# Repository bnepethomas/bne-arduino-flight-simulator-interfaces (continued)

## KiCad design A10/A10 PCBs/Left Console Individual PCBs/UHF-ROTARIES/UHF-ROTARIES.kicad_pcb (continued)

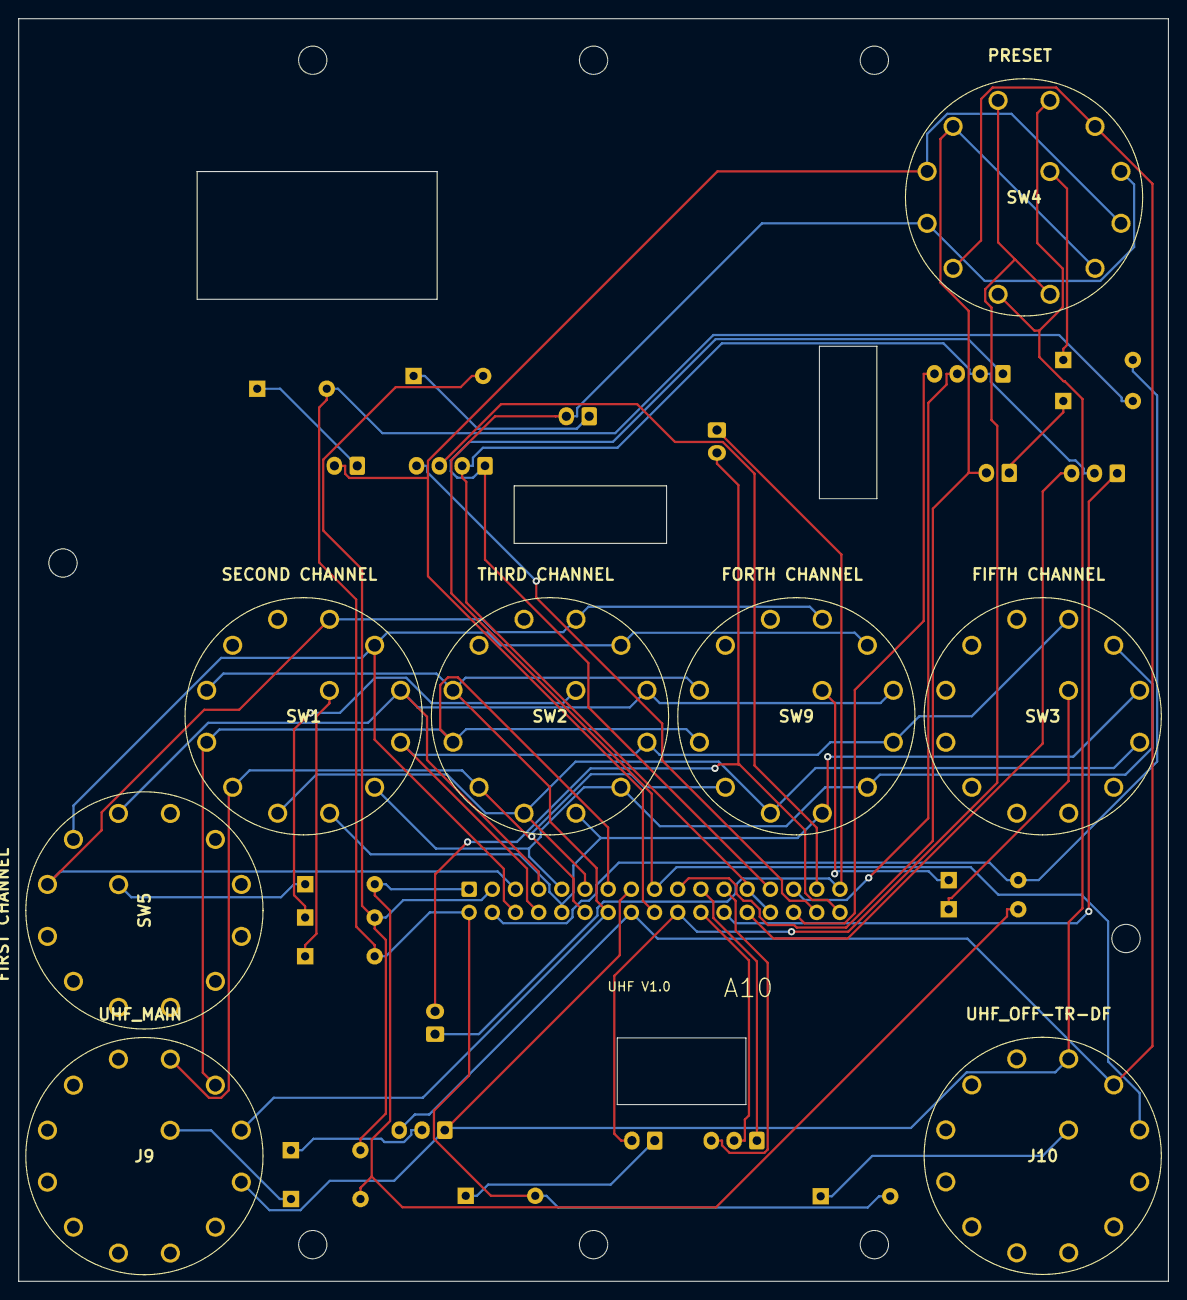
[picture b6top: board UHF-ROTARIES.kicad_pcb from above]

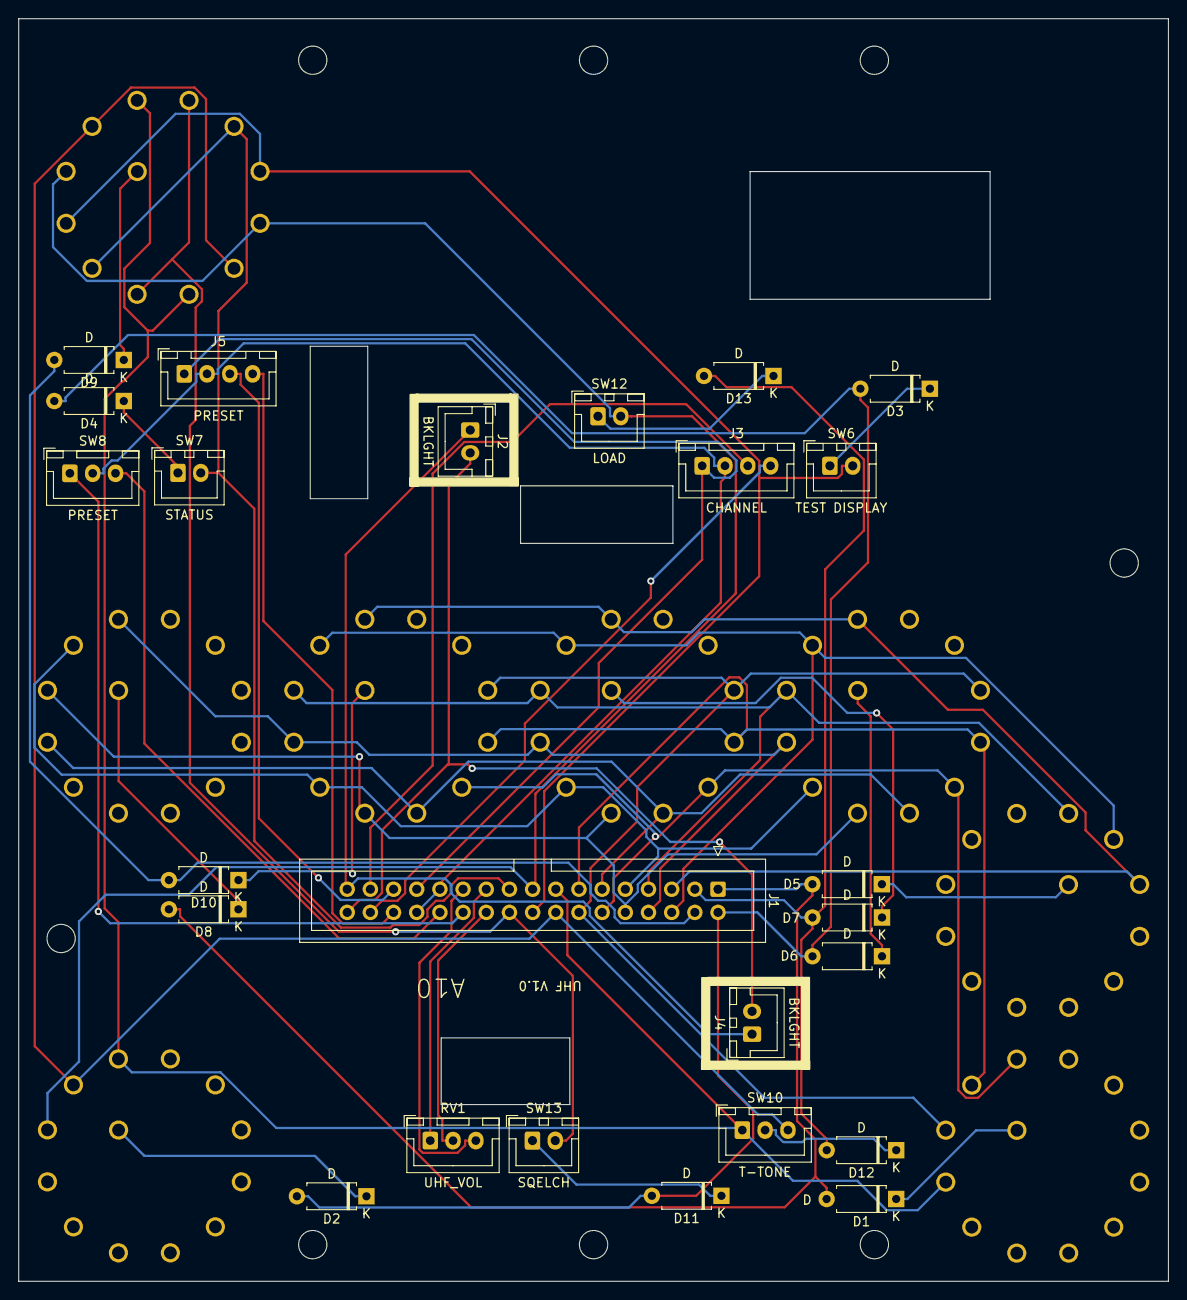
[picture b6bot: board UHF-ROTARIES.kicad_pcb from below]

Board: 2 copper layers, 126.0 x 138.4 mm, 33 parts (25 on the bottom side), 46 nets.

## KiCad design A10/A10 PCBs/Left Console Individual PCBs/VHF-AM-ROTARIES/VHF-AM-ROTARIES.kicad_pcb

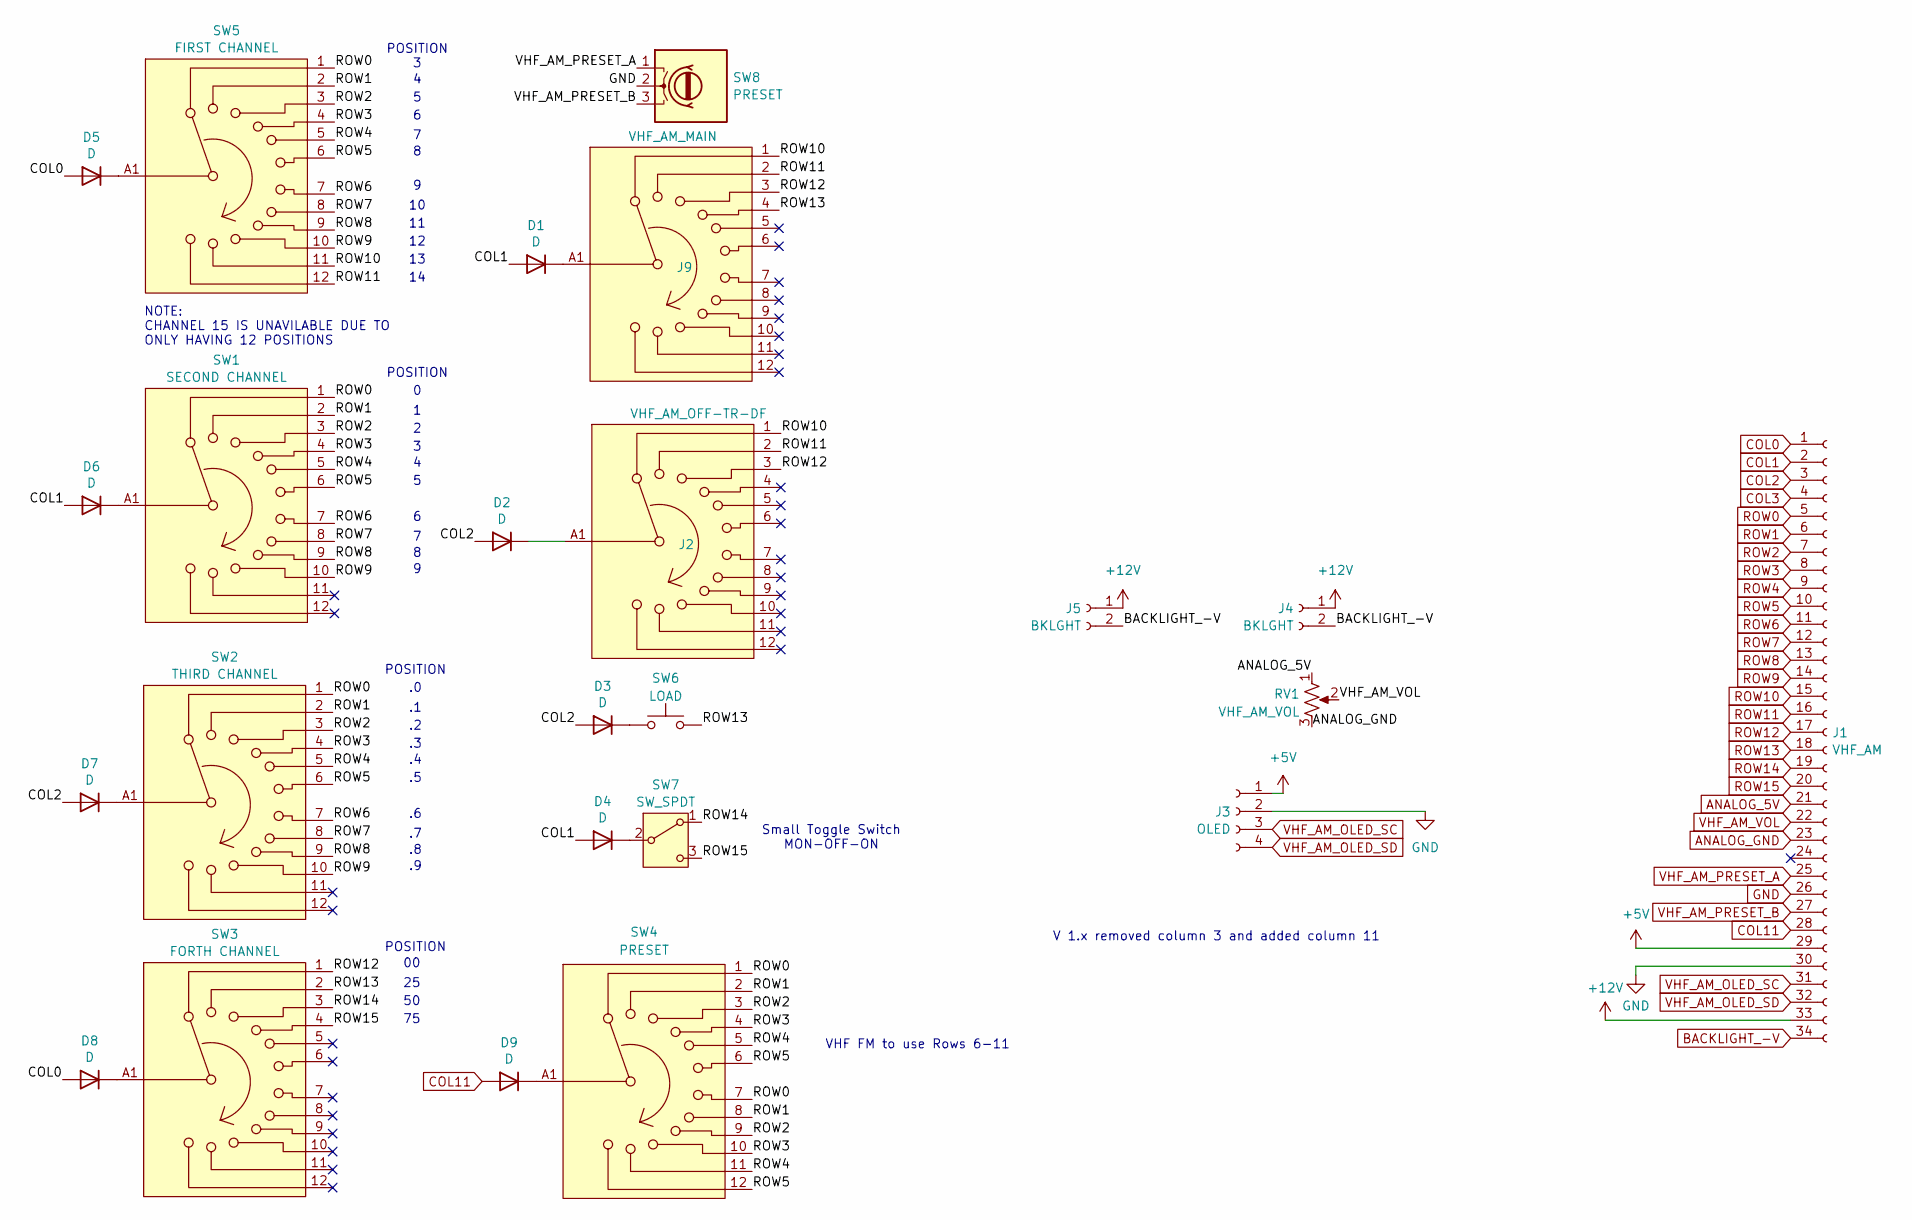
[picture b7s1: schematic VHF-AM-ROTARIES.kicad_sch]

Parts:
D1, D2, D3, D4, D5, D6, D7, D8, D9: D; D_A-405_P7.62mm_Horizontal
J1: VHF_AM; IDC-Header_2x17_P2.54mm_Vertical
J2: VHF_AM_OFF-TR-DF; ALPHA 12 POS
J3: OLED; JST_XH_B4B-XH-A_1x04_P2.50mm_Vertical
J4, J5: BKLGHT; JST_XH_B2B-XH-A_1x02_P2.50mm_Vertical
J9: VHF_AM_MAIN; ALPHA 12 POS
RV1: VHF_AM_VOL; JST_XH_B3B-XH-A_1x03_P2.50mm_Vertical
SW1: SECOND CHANNEL; ALPHA 12 POS
SW2: THIRD CHANNEL; ALPHA 12 POS
SW3: FORTH CHANNEL; ALPHA 12 POS
SW4: PRESET; ALPHA 12 POS
SW5: FIRST CHANNEL; ALPHA 12 POS
SW6: LOAD; JST_XH_B2B-XH-A_1x02_P2.50mm_Vertical
SW7: SW_SPDT; JST_XH_B3B-XH-A_1x03_P2.50mm_Vertical
SW8: PRESET; JST_XH_B3B-XH-A_1x03_P2.50mm_Vertical

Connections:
+5V: J1.29, J3.1
+12V: J1.33, J4.1, J5.1
ANALOG_5V: J1.21, RV1.1
ANALOG_GND: J1.23, RV1.3
BACKLIGHT_-V: J1.34, J4.2, J5.2
COL0: D5.2 (A), D8.2 (A), J1.1
COL1: D1.2 (A), D4.2 (A), D6.2 (A), J1.2
COL2: D2.2 (A), D3.2 (A), D7.2 (A), J1.3
GND: J1.26, J1.30, J3.2, SW8.2
unnamed: D1.1 (K), J9.A1
unnamed: D2.1 (K), J2.A1
unnamed: D3.1 (K), SW6.1
unnamed: D4.1 (K), SW7.2 (B)
unnamed: D5.1 (K), SW5.A1
unnamed: D6.1 (K), SW1.A1
unnamed: D7.1 (K), SW2.A1
unnamed: D8.1 (K), SW3.A1
unnamed: D9.1 (K), SW4.A1
ROW0: J1.5, SW1.1, SW2.1, SW4.1, SW4.7, SW5.1
ROW1: J1.6, SW1.2, SW2.2, SW4.2, SW4.8, SW5.2
ROW2: J1.7, SW1.3, SW2.3, SW4.3, SW4.9, SW5.3
ROW3: J1.8, SW1.4, SW2.4, SW4.4, SW4.10, SW5.4
ROW4: J1.9, SW1.5, SW2.5, SW4.5, SW4.11, SW5.5
ROW5: J1.10, SW1.6, SW2.6, SW4.6, SW4.12, SW5.6
ROW6: J1.11, SW1.7, SW2.7, SW5.7
ROW7: J1.12, SW1.8, SW2.8, SW5.8
ROW8: J1.13, SW1.9, SW2.9, SW5.9
ROW9: J1.14, SW1.10, SW2.10, SW5.10
ROW10: J1.15, J2.1, J9.1, SW5.11
ROW11: J1.16, J2.2, J9.2, SW5.12
ROW12: J1.17, J2.3, J9.3, SW3.1
ROW13: J1.18, J9.4, SW3.2, SW6.2
ROW14: J1.19, SW3.3, SW7.1 (A)
ROW15: J1.20, SW3.4, SW7.3 (C)
VHF_AM_OLED_SC: J1.31, J3.3
VHF_AM_OLED_SD: J1.32, J3.4
VHF_AM_PRESET_A: J1.25, SW8.1
VHF_AM_PRESET_B: J1.27, SW8.3
VHF_AM_VOL: J1.22, RV1.2

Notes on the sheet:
VHF FM to use Rows 6-11
NOTE: CHANNEL 15 IS UNAVILABLE DUE TO ONLY HAVING 12 POSITIONS
POSITION
V 1.x removed column 3 and added column 11
Small Toggle Switch MON-OFF-ON

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
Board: 2 copper layers, 24 parts (17 on the bottom side), 40 nets, no tracks yet.

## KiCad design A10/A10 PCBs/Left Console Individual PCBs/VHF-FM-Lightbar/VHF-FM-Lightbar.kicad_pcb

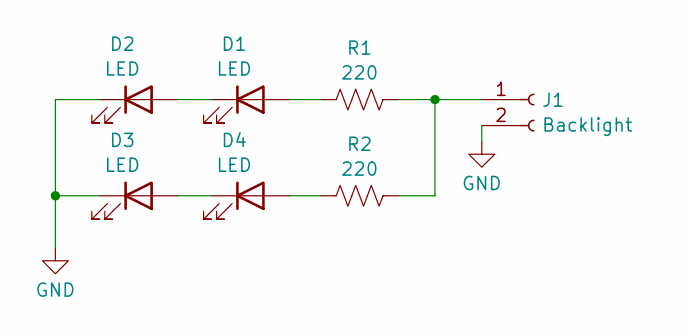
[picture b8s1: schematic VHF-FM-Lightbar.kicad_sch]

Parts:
D1, D2, D3, D4: LED; LED_D3.0mm_FlatTop
J1: Backlight; JST_XH_B2B-XH-A_1x02_P2.50mm_Vertical
R1, R2: 220; R_Axial_DIN0204_L3.6mm_D1.6mm_P5.08mm_Vertical

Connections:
GND: D2.1 (K), D3.1 (K), J1.2
unnamed: D1.2 (A), R1.1
unnamed: D1.1 (K), D2.2 (A)
unnamed: D3.2 (A), D4.1 (K)
unnamed: D4.2 (A), R2.1
unnamed: J1.1, R1.2, R2.2

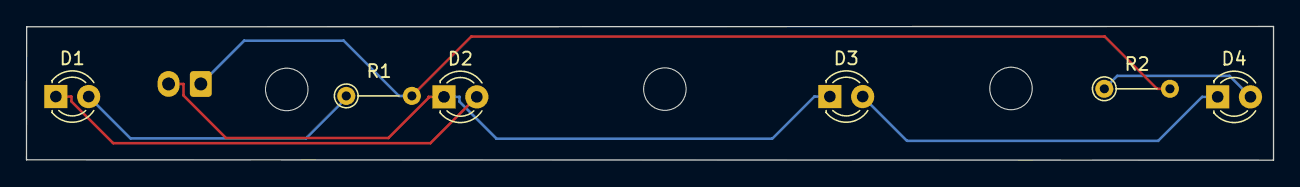
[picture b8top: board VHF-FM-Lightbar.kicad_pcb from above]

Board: 2 copper layers, 96.5 x 10.3 mm, 7 parts (1 on the bottom side), 6 nets.
